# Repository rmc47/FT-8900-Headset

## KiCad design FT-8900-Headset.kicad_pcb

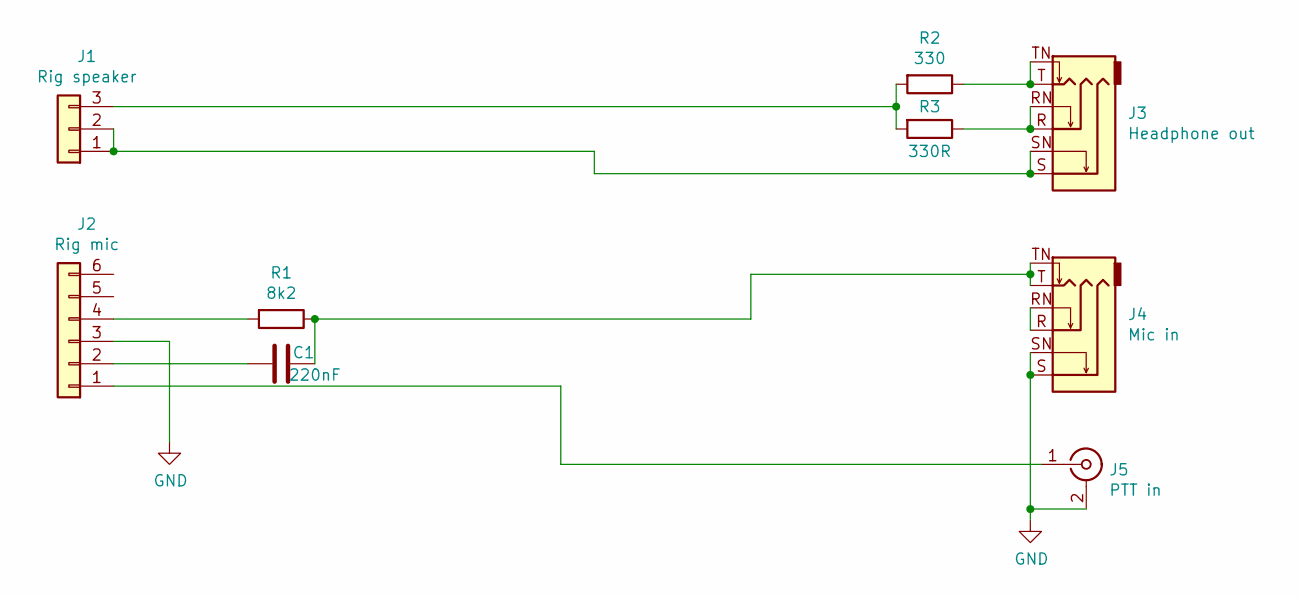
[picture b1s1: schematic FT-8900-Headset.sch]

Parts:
C1: 220nF; C_0805_2012Metric_Pad1.15x1.40mm_HandSolder
J1: Rig speaker; PinHeader_1x03_P2.54mm_Vertical
J2: Rig mic; PinHeader_1x06_P2.54mm_Vertical
J3: Headphone out; Cliff_FCR1295_S9_BBB_3.5mm_Jack_Stereo
J4: Mic in; Cliff_FCR1295_S9_BBB_3.5mm_Jack_Stereo
J5: PTT in; rca_red
R1: 8k2; R_0805_2012Metric_Pad1.15x1.40mm_HandSolder
R2: 330; R_0805_2012Metric_Pad1.15x1.40mm_HandSolder
R3: 330R; R_0805_2012Metric_Pad1.15x1.40mm_HandSolder

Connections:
GND: J2.3, J4.S, J4.SN, J5.2 (Ext)
unnamed: C1.1, J4.T, J4.TN, R1.1
unnamed: C1.2, J2.2
unnamed: J1.1, J1.2, J3.S, J3.SN
unnamed: J1.3, R2.2, R3.2
unnamed: J2.1, J5.1 (In)
unnamed: J2.4, R1.2
unnamed: J3.R, J3.RN, R3.1
unnamed: J3.T, J3.TN, R2.1
unnamed: J4.R, J4.RN

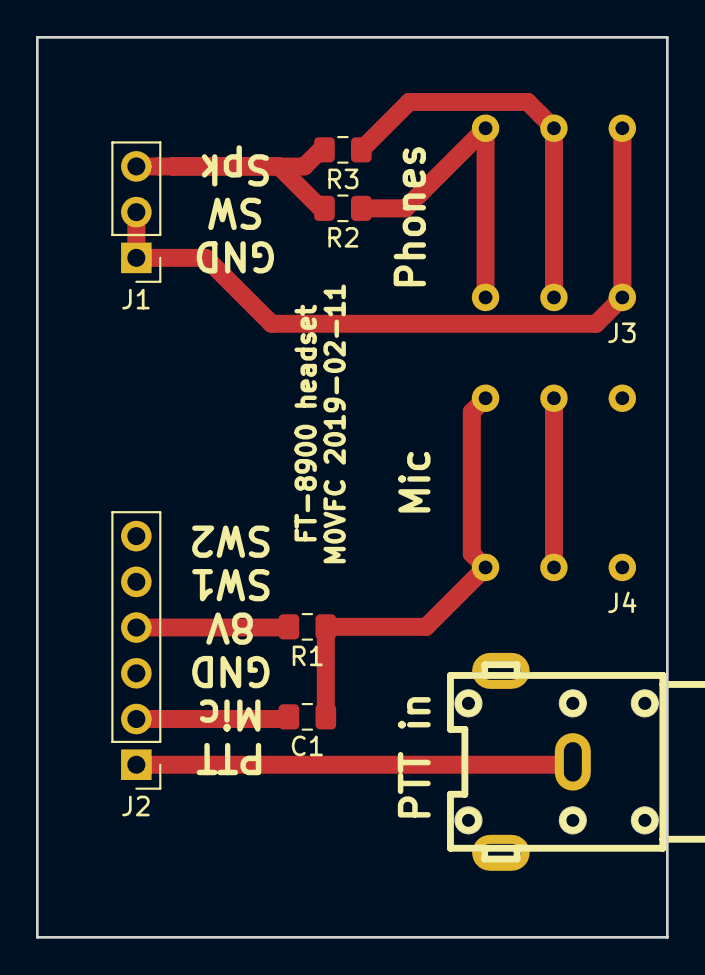
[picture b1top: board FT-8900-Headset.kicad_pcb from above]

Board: 2 copper layers, 35.0 x 50.0 mm, 9 parts (0 on the bottom side), 10 nets.
